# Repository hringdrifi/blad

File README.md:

The previous HY0020-based version is available in the [blad-hy0020 repository](https://github.com/hringdrifi/blad-hy0020).

Blað is a compact wireless keyboard design project by [hringdrifi](https://github.com/hringdrifi).

The design uses 42 Kailh Choc hot-swap switch positions and a [MinewSemi MS88SF21](https://en.minewsemi.com/bluetooth-module/nrf52840ms88sf21) wireless module. Development is currently targeting the MS88SF21 variant based on the Nordic nRF52840.

## Supported components

The design supports the following keyboard components:

- Kailh Choc V2 switches
- Kailh low-profile sockets
- [Chosfox Cross-Core Low-Profile Stabilizers](https://chosfox.com/products/chosfox-cross-core-satellite-switch-for-low-profile-keyboards)

All PCB components can be soldered by hand, so no reflow oven is required for assembly.

Confirm the exact part variants and mechanical fit before ordering or manufacturing.

## Connectivity and firmware

Blað is intended to support both Bluetooth Low Energy (BLE) and USB through the nRF52840-based MS88SF21. It uses a CR1632 lithium coin cell for battery operation. The nRF52840-based MS88SF21 module is TELEC-certified for use in Japan (Giteki compliant).

The MS88SF21 is also available with an nRF52833, but the first hardware and firmware revision in this repository will target the nRF52840 version. Compatibility between the two module variants and with the existing PCB design is still being evaluated; verify the module pinout, footprint, power supply, USB routing, and firmware target before manufacturing hardware.

## Project status

This repository is being migrated from the previous FDK HY0020/nRF52832 design to the MS88SF21/nRF52840. The current KiCad and case files may still contain HY0020-specific circuitry, footprints, markings, dimensions, or other assumptions and should not yet be treated as a completed MS88SF21 design.

Validate the module variant, PCB compatibility, USB implementation, switches, battery, firmware, manufacturing process, and assembly before building hardware.

## Available files

- [`pcb/`](pcb/) — KiCad source files for the keyboard PCB and plates
  - [`blad.kicad_pcb`](pcb/blad.kicad_pcb) — main keyboard PCB
  - [`blad.kicad_sch`](pcb/blad.kicad_sch) — schematic
  - [`blad_switch_plate.kicad_pcb`](pcb/blad_switch_plate.kicad_pcb) — switch plate PCB
  - [`blad_bottom_plate.kicad_pcb`](pcb/blad_bottom_plate.kicad_pcb) — bottom plate PCB
  - [`smidr.pretty/`](pcb/smidr.pretty/) — custom footprints referenced by the design
  - [`3dmodels/`](pcb/3dmodels/) — STEP models for selected components
- [`case/`](case/) — STEP models for the case assembly
  - [`blad_switch_plate.step`](case/blad_switch_plate.step) — case switch plate
  - [`blad_bumper.step`](case/blad_bumper.step) — bumper layer
- [`pcb/README.md`](pcb/README.md) — Smiðr KiCad-export details
- [`case/README.md`](case/README.md) — case-model notes and file roles

## License

The design data in `pcb/` and `case/` is licensed under the [CERN Open Hardware Licence Version 2 - Permissive (CERN-OHL-P-2.0)](LICENSE).

This license permits use, modification, manufacture, and sale of the design data and products made from it. Modified design data does not need to be published, but applicable notices must be retained and modifications must be documented. The design data and any resulting products are provided without warranty.

## Disclaimer

Verify dimensions, clearances, component compatibility, manufacturability, and safety for your own build before making any parts. Use of these files is at your own risk.

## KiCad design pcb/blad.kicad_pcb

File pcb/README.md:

# Blað KiCad export

Generated by Smiðr.

This KiCad export places center-origin Smiðr switch footprints from the physical layout and emits a matching schematic with keyboard matrix nets.

- Plate PCB: blad_switch_plate.kicad_pcb contains center-origin key-hole footprints for the same physical layout.
- Switch footprint: Smidr:SW_Smidr_Choc_Hotswap
- Diode footprint: Smidr:D_Smidr_SOD123
- Footprint library: smidr.pretty is included in this ZIP and referenced by fp-lib-table.
- Switch outlines: keycap, fab, and courtyard geometry are generated from each key's w/h.
- RGB Matrix: no per-key RGB LEDs placed.
- Backlight: no per-key backlight LEDs placed.
- Direct-pin projects connect each switch between its direct GPIO net and GND.
- Matrix projects connect switches and diodes using ROWn/COLn nets.
- MS88SF21 symbol: `Smidr:MinewSemi_nRF52840_MS88SF21_5V_USB_Available` follows the MinewSemi Store product name `nRF52840-MS88SF21` and its `5V / USB Available` variant; the manufacturer hardware code `1Y40AI-U` is retained in the `Hardware Code` property.
- MS88SF21 footprint: `Smidr:RF_Module_MinewSemi_MS88SF21` uses the manufacturer's 1.8 x 0.8 mm recommended lands and includes the PCB-antenna keepout.
- MS88SF21 3D model: `smidr.3dshapes/MS88SF21.step` is generated locally from the manufacturer dimensions by `scripts/generate_ms88sf21_step.py`.
- The MS88SF21 library assets are available for migration, but the existing HY0020 circuit and board placement have not been replaced yet.
- Distributor order codes and module hardware codes are intentionally not used as the primary symbol name; record them as supplier-specific purchasing data when needed.

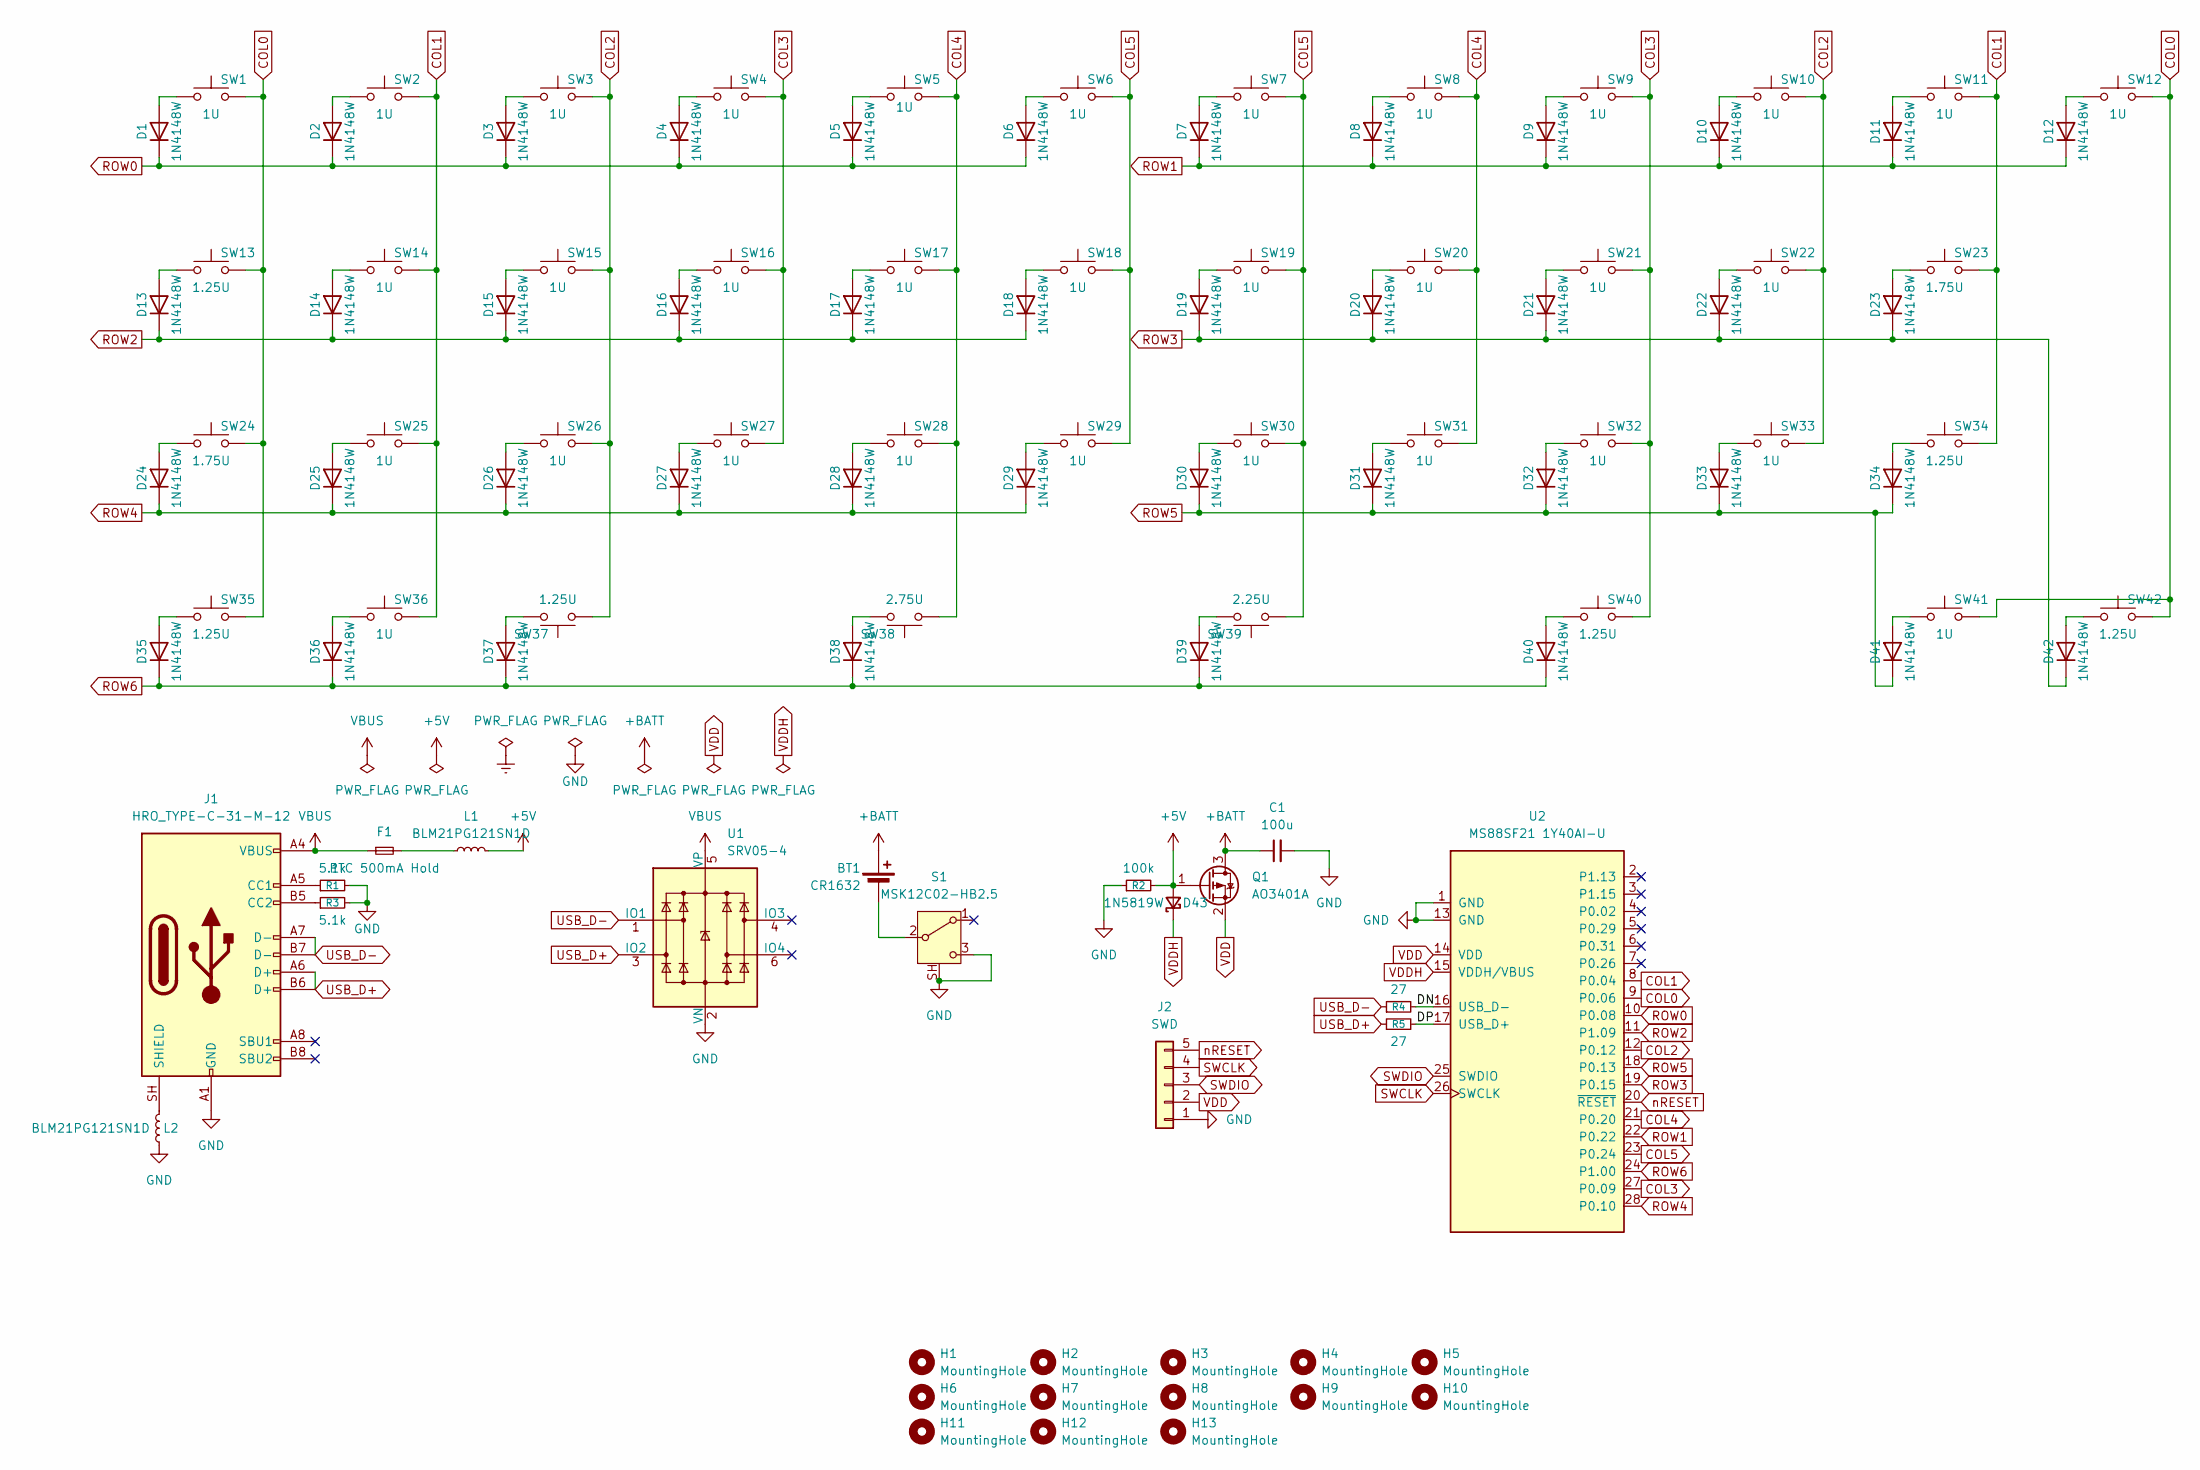
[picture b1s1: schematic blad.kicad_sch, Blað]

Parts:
BT1: CR1632; BatteryHolder_Takachi_BS-S-1632
C1: 100u; C_1206_3216Metric; JLCPCB Part # C15008
D1, D2, D3, D4, D5, D6, D7, D8, D9, D10, D11, D12, D13, D14, D15, D16, D17, D18, D19, D20, D21, D22, D23, D24, D25, D26, D27, D28, D29, D30, D31, D32, D33, D34, D35, D36, D37, D38, D39, D40, D41, D42: 1N4148W; D_SOD-123
D43: 1N5819W; D_SOD-123; JLCPCB Part # C2988774
F1: PTC 500mA Hold; Fuse_1206_3216Metric; JLCPCB Part # C151162
H1, H2, H3, H4, H5, H6, H7, H8, H9, H10, H11, H12, H13: MountingHole; MountingHole_2.1mm
J1: HRO_TYPE-C-31-M-12; USB_C_Receptacle_HRO_TYPE-C-31-M-12; JLCPCB Part # C165948
J2: SWD; PinHeader_1x05_P1.27mm_Vertical
L1, L2: BLM21PG121SN1D; L_0805_2012Metric; JLCPCB Part # C79382
Q1: AO3401A; SOT-23; JLCPCB Part # C15127
R1, R3: 5.1k; R_0603_1608Metric; JLCPCB Part # C23186
R2: 100k; R_0603_1608Metric; JLCPCB Part # C25803
R4, R5: 27; R_0603_1608Metric; JLCPCB Part # C25190
S1: MSK12C02-HB2.5; SW_SPDT_Shouhan_MSK12C02; JLCPCB Part # C47020937
SW1, SW2, SW3, SW4, SW5, SW6, SW7, SW8, SW9, SW10, SW11, SW12, SW14, SW15, SW16, SW17, SW18, SW19, SW20, SW21, SW22, SW25, SW26, SW27, SW28, SW29, SW30, SW31, SW32, SW33, SW36, SW41: 1U; SW_Smidr_Choc_Hotswap
SW13, SW34, SW35, SW37, SW40, SW42: 1.25U; SW_Smidr_Choc_Hotswap
SW23, SW24: 1.75U; SW_Smidr_Choc_Hotswap
SW38: 2.75U; SW_Smidr_Choc_Hotswap
SW39: 2.25U; SW_Smidr_Choc_Hotswap
U1: SRV05-4; SOT-23-6; JLCPCB Part # C7420376
U2: MS88SF21 1Y40AI-U; RF_Module_MinewSemi_MS88SF21; MPN 1Y40AI-U

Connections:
+5V: D43.2 (A), L1.2, Q1.1 (G), R2.2
+BATT: BT1.1 (+), C1.1, Q1.3 (D)
/DN: R4.2, U2.16 (USB_D-)
/DP: R5.2, U2.17 (USB_D+)
COL0: SW1.2, SW12.2, SW13.2, SW24.2, SW35.2, SW41.2, SW42.2, U2.9 (P0.06)
COL1: SW2.2, SW11.2, SW14.2, SW23.2, SW25.2, SW34.2, SW36.2, U2.8 (P0.04)
COL2: SW3.2, SW10.2, SW15.2, SW22.2, SW26.2, SW33.2, SW37.1, U2.12 (P0.12)
COL3: SW4.2, SW9.2, SW16.2, SW21.2, SW27.2, SW32.2, SW40.2, U2.27 (P0.09)
COL4: SW5.2, SW8.2, SW17.2, SW20.2, SW28.2, SW31.2, SW38.1, U2.21 (P0.20)
COL5: SW6.2, SW7.2, SW18.2, SW19.2, SW29.2, SW30.2, SW39.1, U2.23 (P0.24)
GND: C1.2, J1.A1 (GND), J1.A12 (GND), J1.B1 (GND), J1.B12 (GND), J2.1, L2.1, R1.2, R2.1, R3.2, S1.3 (C), S1.SH, U1.2 (VN), U2.1 (GND), U2.13 (GND)
unnamed: BT1.2 (-), S1.2 (B)
unnamed: D1.2 (A), SW1.1
unnamed: D2.2 (A), SW2.1
unnamed: D3.2 (A), SW3.1
unnamed: D4.2 (A), SW4.1
unnamed: D5.2 (A), SW5.1
unnamed: D6.2 (A), SW6.1
unnamed: D7.2 (A), SW7.1
unnamed: D8.2 (A), SW8.1
unnamed: D9.2 (A), SW9.1
unnamed: D10.2 (A), SW10.1
unnamed: D11.2 (A), SW11.1
unnamed: D12.2 (A), SW12.1
unnamed: D13.2 (A), SW13.1
unnamed: D14.2 (A), SW14.1
unnamed: D15.2 (A), SW15.1
unnamed: D16.2 (A), SW16.1
unnamed: D17.2 (A), SW17.1
unnamed: D18.2 (A), SW18.1
unnamed: D19.2 (A), SW19.1
unnamed: D20.2 (A), SW20.1
unnamed: D21.2 (A), SW21.1
unnamed: D22.2 (A), SW22.1
unnamed: D23.2 (A), SW23.1
unnamed: D24.2 (A), SW24.1
unnamed: D25.2 (A), SW25.1
unnamed: D26.2 (A), SW26.1
unnamed: D27.2 (A), SW27.1
unnamed: D28.2 (A), SW28.1
unnamed: D29.2 (A), SW29.1
unnamed: D30.2 (A), SW30.1
unnamed: D31.2 (A), SW31.1
unnamed: D32.2 (A), SW32.1
unnamed: D33.2 (A), SW33.1
unnamed: D34.2 (A), SW34.1
unnamed: D35.2 (A), SW35.1
unnamed: D36.2 (A), SW36.1
unnamed: D37.2 (A), SW37.2
unnamed: D38.2 (A), SW38.2
unnamed: D39.2 (A), SW39.2
unnamed: D40.2 (A), SW40.1
unnamed: D41.2 (A), SW41.1
unnamed: D42.2 (A), SW42.1
unnamed: F1.2, L1.1
unnamed: J1.A5 (CC1), R1.1
unnamed: J1.B5 (CC2), R3.1
unnamed: J1.SH (SHIELD), L2.2
ROW0: D1.1 (K), D2.1 (K), D3.1 (K), D4.1 (K), D5.1 (K), D6.1 (K), U2.10 (P0.08)
ROW1: D7.1 (K), D8.1 (K), D9.1 (K), D10.1 (K), D11.1 (K), D12.1 (K), U2.22 (P0.22)
ROW2: D13.1 (K), D14.1 (K), D15.1 (K), D16.1 (K), D17.1 (K), D18.1 (K), U2.11 (P1.09)
ROW3: D19.1 (K), D20.1 (K), D21.1 (K), D22.1 (K), D23.1 (K), D42.1 (K), U2.19 (P0.15)
ROW4: D24.1 (K), D25.1 (K), D26.1 (K), D27.1 (K), D28.1 (K), D29.1 (K), U2.28 (P0.10)
ROW5: D30.1 (K), D31.1 (K), D32.1 (K), D33.1 (K), D34.1 (K), D41.1 (K), U2.18 (P0.13)
ROW6: D35.1 (K), D36.1 (K), D37.1 (K), D38.1 (K), D39.1 (K), D40.1 (K), U2.24 (P1.00)
SWCLK: J2.4, U2.26 (SWCLK)
SWDIO: J2.3, U2.25 (SWDIO)
USB_D+: J1.A6 (D+), J1.B6 (D+), R5.1, U1.3 (IO2)
USB_D-: J1.A7 (D-), J1.B7 (D-), R4.1, U1.1 (IO1)
VBUS: F1.1, J1.A4 (VBUS), J1.A9 (VBUS), J1.B4 (VBUS), J1.B9 (VBUS), U1.5 (VP)
VDD: J2.2, Q1.2 (S), U2.14 (VDD)
VDDH: D43.1 (K), U2.15 (VDDH/VBUS)
nRESET: J2.5, U2.20 (~RESET)

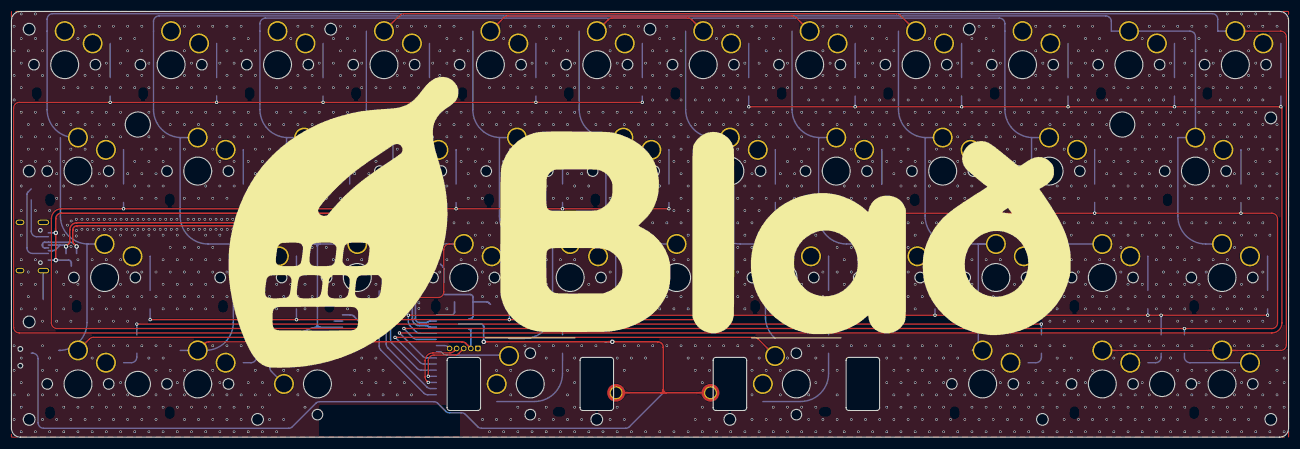
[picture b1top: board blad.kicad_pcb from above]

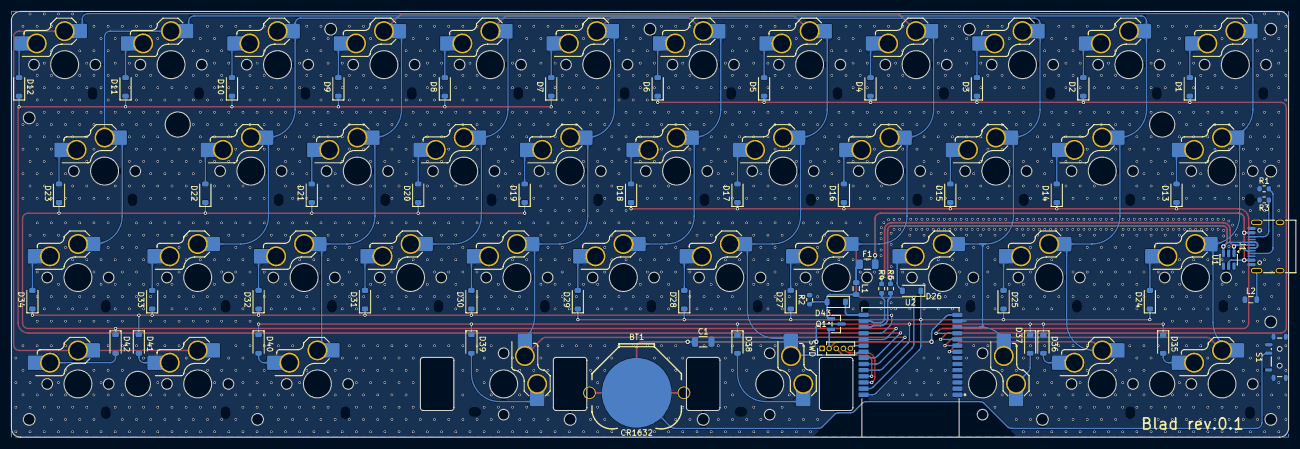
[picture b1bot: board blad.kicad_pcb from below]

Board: 2 copper layers, 228.6 x 76.2 mm, 114 parts (101 on the bottom side), 73 nets.
